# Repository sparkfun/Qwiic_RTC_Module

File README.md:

Qwiic Real Time Clock Module (RV-1805) Module
==================

[*Qwiic RV-1805 RTC Module (BOB-14558)*](https://www.sparkfun.com/products/14558)

Get with the times, already! This SparkFun Real Time Clock (RTC) Module is a Qwiic-enabled breakout board for the RV-1805 chipset. The RTC is ultra-low power (running at only about 22nA in its lowest power setting) so it can use a supercapacitor for backup power instead of a normal battery. This means you get plenty of charge and discharge cycles without any degradation to the “battery.“ To make it even easier to get your readings, all communication is enacted exclusively via I2C, utilizing our handy Qwiic system so no soldering is required to connect it to the rest of your system. However, we still have broken out 0.1”-spaced pins in case you prefer to use a breadboard.

Repository Contents
-------------------
* **/Documents** - Datasheets. 
* **/Hardware** - All Eagle design files (.brd, .sch). 
* **/Production** - Various test jigs and large panel layouts used for production.

Documentation
--------------
* **[Library](https://github.com/sparkfun/SparkFun_RV-1805_Arduino_Library)** - Arduino library for the Qwiic Real Time Clock Module (RV-1805) Module.
* **[Hookup Guide](https://learn.sparkfun.com/tutorials/qwiic-real-time-clock-module-rv-1805-hookup-guide)** - Basic hookup guide.

Product Versions
----------------
* [BOB-14558](https://www.sparkfun.com/products/14558) - SparkFun red version
* [SPX-14642](https://www.sparkfun.com/products/14642) - SparkX version

License Information
-------------------

This product is _**open source**_! 

Please review the LICENSE.md file for license information. 

If you have any questions or concerns on licensing, please contact techsupport@sparkfun.com.

Distributed as-is; no warranty is given.

- Your friends at SparkFun.

_<COLLABORATION CREDIT>_

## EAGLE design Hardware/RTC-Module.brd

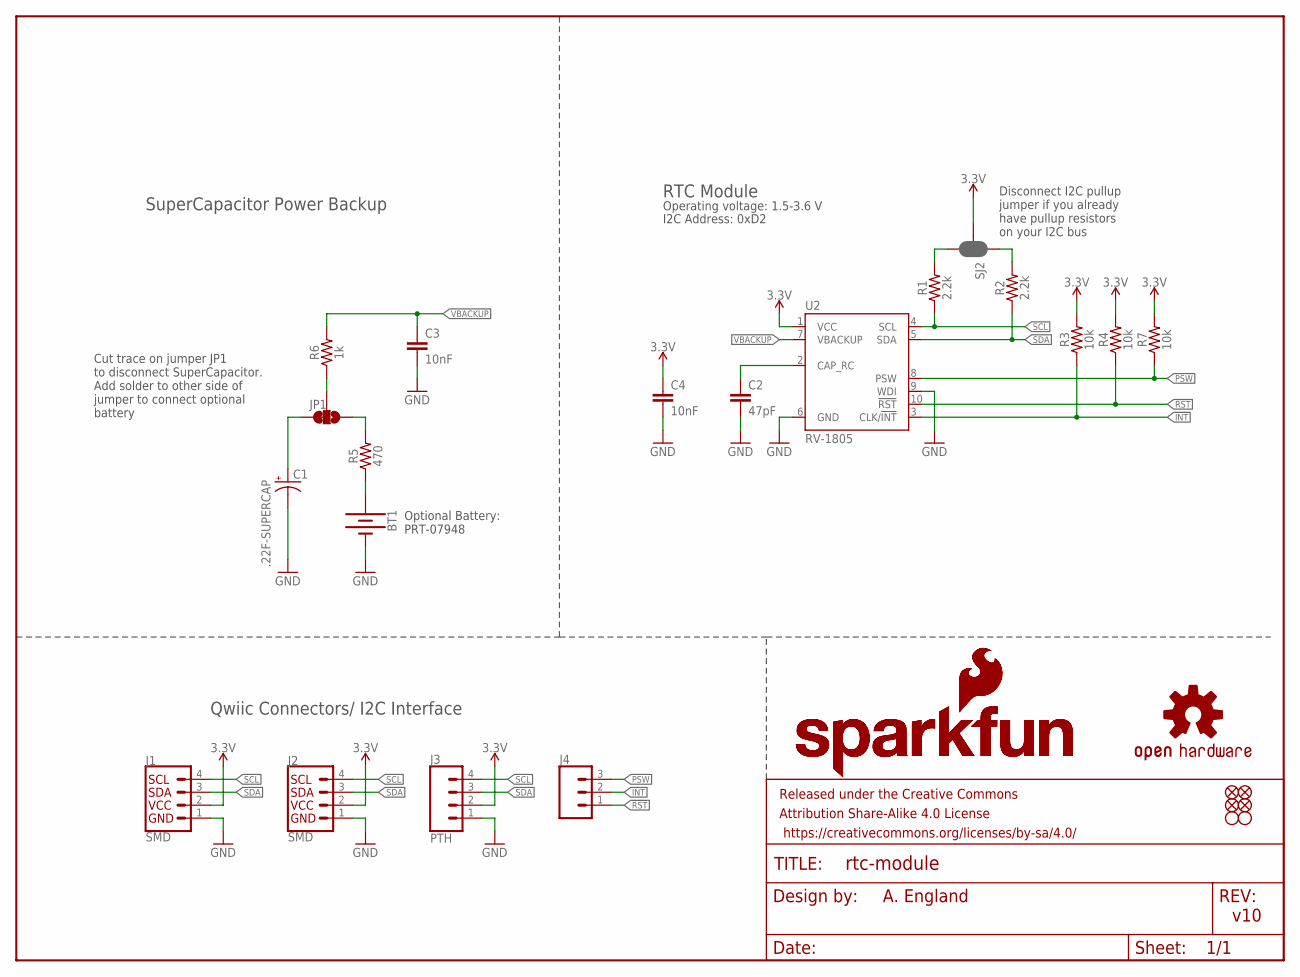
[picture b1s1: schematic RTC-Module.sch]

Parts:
BT1: BATTERY-12MM_PTH; BATTCON_12MM_PTH
C1: .22F-SUPERCAP; DSK-RADIAL-6.8MM
C2: 47pF; 0603
C3, C4: 10nF; 0603
FD1, FD2, FD3, FD4: FIDUCIALUFIDUCIAL; FIDUCIAL-MICRO
FRAME2: FRAME-LETTER; CREATIVE_COMMONS
J1, J2: SMD; 1X04_1MM_RA
J3: PTH; 1X04_NO_SILK
J4: CONN_031X03_NO_SILK; 1X03_NO_SILK
JP1: JUMPER-SMT_3_1-NC_TRACE_NO-SILK; SMT-JUMPER_3_1-NC_TRACE_NO-SILK
LOGO1: OSHW-LOGOS; OSHW-LOGO-S
LOGO2, LOGO3: SFE_LOGO_NAME_FLAME.1_INCH; SFE_LOGO_NAME_FLAME_.1
R1, R2: 2.2k; 0603
R3, R4, R7: 10k; 0603
R5: 470; 0603
R6: 1k; 0603
SJ2: JUMPER-SMT_3_2-NC_PASTE_SILK; SMT-JUMPER_3_2-NC_PASTE_SILK
U2: RV-1805
U$6, U$7: STAND-OFF

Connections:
3.3V: C4.1, J1.2, J2.2, J3.2, R3.2, R4.2, R7.2, SJ2.2, U2.1 (VCC)
!INT: J4.2, R3.1, U2.3 (CLK/!INT)
!RST: J4.1, R4.1, U2.10 (!RST)
GND: BT1.GND (-), C1.-, C2.2, C3.2, C4.2, J1.1, J2.1, J3.1, U2.6 (GND), U2.9 (WDI)
unnamed: R1.2, SJ2.3
unnamed: R2.2, SJ2.1
unnamed: BT1.VCC@1 (+), R5.1
unnamed: C2.1, U2.2 (CAP_RC)
unnamed: JP1.2, R6.1
unnamed: C1.+, JP1.3
unnamed: JP1.1, R5.2
PSW: J4.3, R7.1, U2.8 (PSW)
SCL: J1.4, J2.4, J3.4, R1.1, U2.4 (SCL)
SDA: J1.3, J2.3, J3.3, R2.1, U2.5 (SDA)
VBACKUP: C3.1, R6.2, U2.7 (VBACKUP)

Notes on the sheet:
v10
A. England
SuperCapacitor Power Backup
RTC Module
Qwiic Connectors/ I2C Interface
Cut trace on jumper JP1 to disconnect SuperCapacitor. Add solder to other side of jumper to connect optional battery
Operating voltage: 1.5-3.6 V
Disconnect I2C pullup jumper if you already have pullup resistors on your I2C bus
I2C Address: 0xD2
Optional Battery: PRT-07948

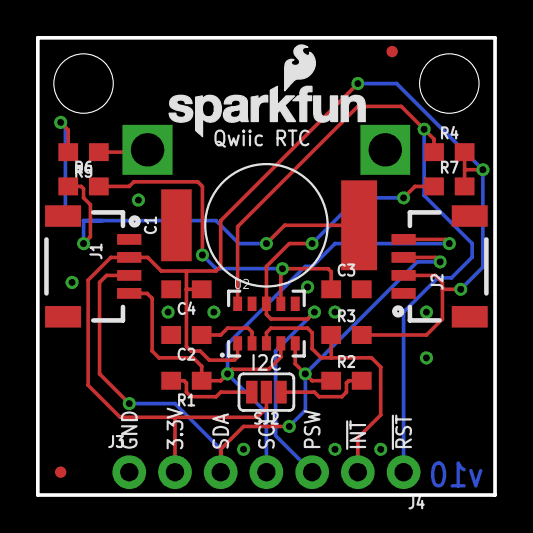
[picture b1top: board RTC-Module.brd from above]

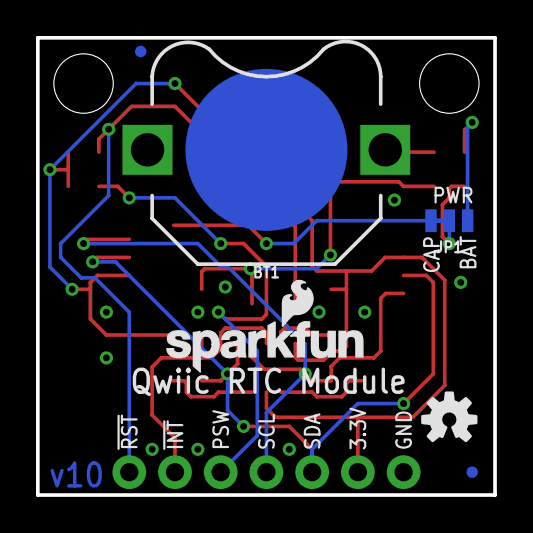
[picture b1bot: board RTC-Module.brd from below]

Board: 2 copper layers, 25.4 x 25.4 mm, 29 parts (6 on the bottom side), 15 nets.

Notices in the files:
parts and their libraries:
SparkFun-Capacitors: Licensing: CC v3.0 Share-Alike You are welcome to use this library for commercial purposes.
SparkFun-Connectors: Licensing: Creative Commons ShareAlike 4.0 International - https://creativecommons.org/licenses/by-sa/4.0
SparkFun-Aesthetics: Released under the Creative Commons
